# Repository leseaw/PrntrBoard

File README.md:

Prntr Board V1
======================
PrntrBoard is a 3D printer controller board designed to work as a shield to STM32 NUCLEO-64 F446 dev kit.

Some features of the board:
-----
  + 5x Trinamic super quiet drivers (TMC2130 or TMC2660)
  + Marlin firmware
  + (2+2) controllable fans and 2x "always on" fan connectors
  + 3x min and max endstops for the x, y and z axis
  + 2x end stops for fillament end detection
  + SPI lcd connector for ST7735 screen
  + Dual thermocouple connectors (for MAX31866, MAX31855 or MAX6675 boards)
  + selectable fan voltage (5V or Vin)

Because the NUCLEO-64 has limited number of IO pins, some compromises had to be made:
  + No sd-card
  + The thermocouple connectors share pins with the E0 and E1 cool fan controls. You'll have to decide to use one or the other via jumpers on the board. Most printers I've seen come with "always on" extruder fans, the choice seemed like a worthy sacrifice.

Generic shortcuts I don't plan to improve:
------
  + 5V power supply is external. These are available from various resellers and fairly cheap - less than $1. No need to waste board layout space and component count.
  + Heated bed MOSFET - large heated beds consume a lot of power and it is challenging to provision the design for > 10A current. External heated bed MOSFETs are very affordable < $10 and claim to support 20A minimum. If you have large bet use one.

Details
------
I use the daily build of KiCad (soon to be released V5) - let me know if you have trouble opening the files.

The current PCB desing is using 4 layer board, 6/6 mil track width/clearance, 12 mil min via hole size and 20 mil via diameter.

There are two active branches:
  + tmc2130 - the board design for TMC2130 drivers
  + tmc2660 - the board design for TMC2660 drivers
  + branches with -r\<digit> sufix are snapshots of boards I have ordered. I only do "minimal" changes there to generate better manufacturing files (for example renaming a component).

Both PCB designs use the QFP version of the driver ICs, because they can handle a bit more power.

Status
------
Rev2 is the current working version. Rev1 had a bug in the endstop input design, other that that it is able to control a 3D printer successfully. I'm considering a re-design of the layout - swapping the location of the 5V input connector and the E1 driver. The driver is crammed in the corner and there was not a lot of space for heat disipation, by moving it to the right there is more breading room. Also considering rotating the NUCLEO board, so it does not stick up in this unpleasant manner.

Tested circuits:
  + Heater control
  + Thermistor input
  + Fan control
  + Motor driver control
  + End stops

Circuits that need verification:
  + Stall guard alert from the motor driver
  + Z probe
  + LCD interface (I noticed this may interfere with the 32k chrystal on the nucleo board)
  + Thermocuple interface

Software
------

The software for the board is a clone of Marlin at [bugfix-2.0.x branch](https://github.com/ghent360/Marlin/tree/bugfix-2.0.x/ "Github.com") of my repository. I keep it relatively in sync with the Marlin branch. *Note: there are other branches of Marlin as well only the bugfix-2.0.x supports the STM32 microcontroller.*

Marlin is using Adruino IDE or Platform IO. I personally had issues with Platform IO not supporting the STM32F4 board, so I use Arduino version 1.8.5. To compile the firmware code you would need to install the [STM32 Arduino port](https://github.com/stm32duino/Arduino_Core_STM32 "www.stm32duino.com").

Visit [my blog](http://blog.pcbxprt.com/) for status updates on the development of the board. I have video of the board controlling a Duplicator I3 mini.

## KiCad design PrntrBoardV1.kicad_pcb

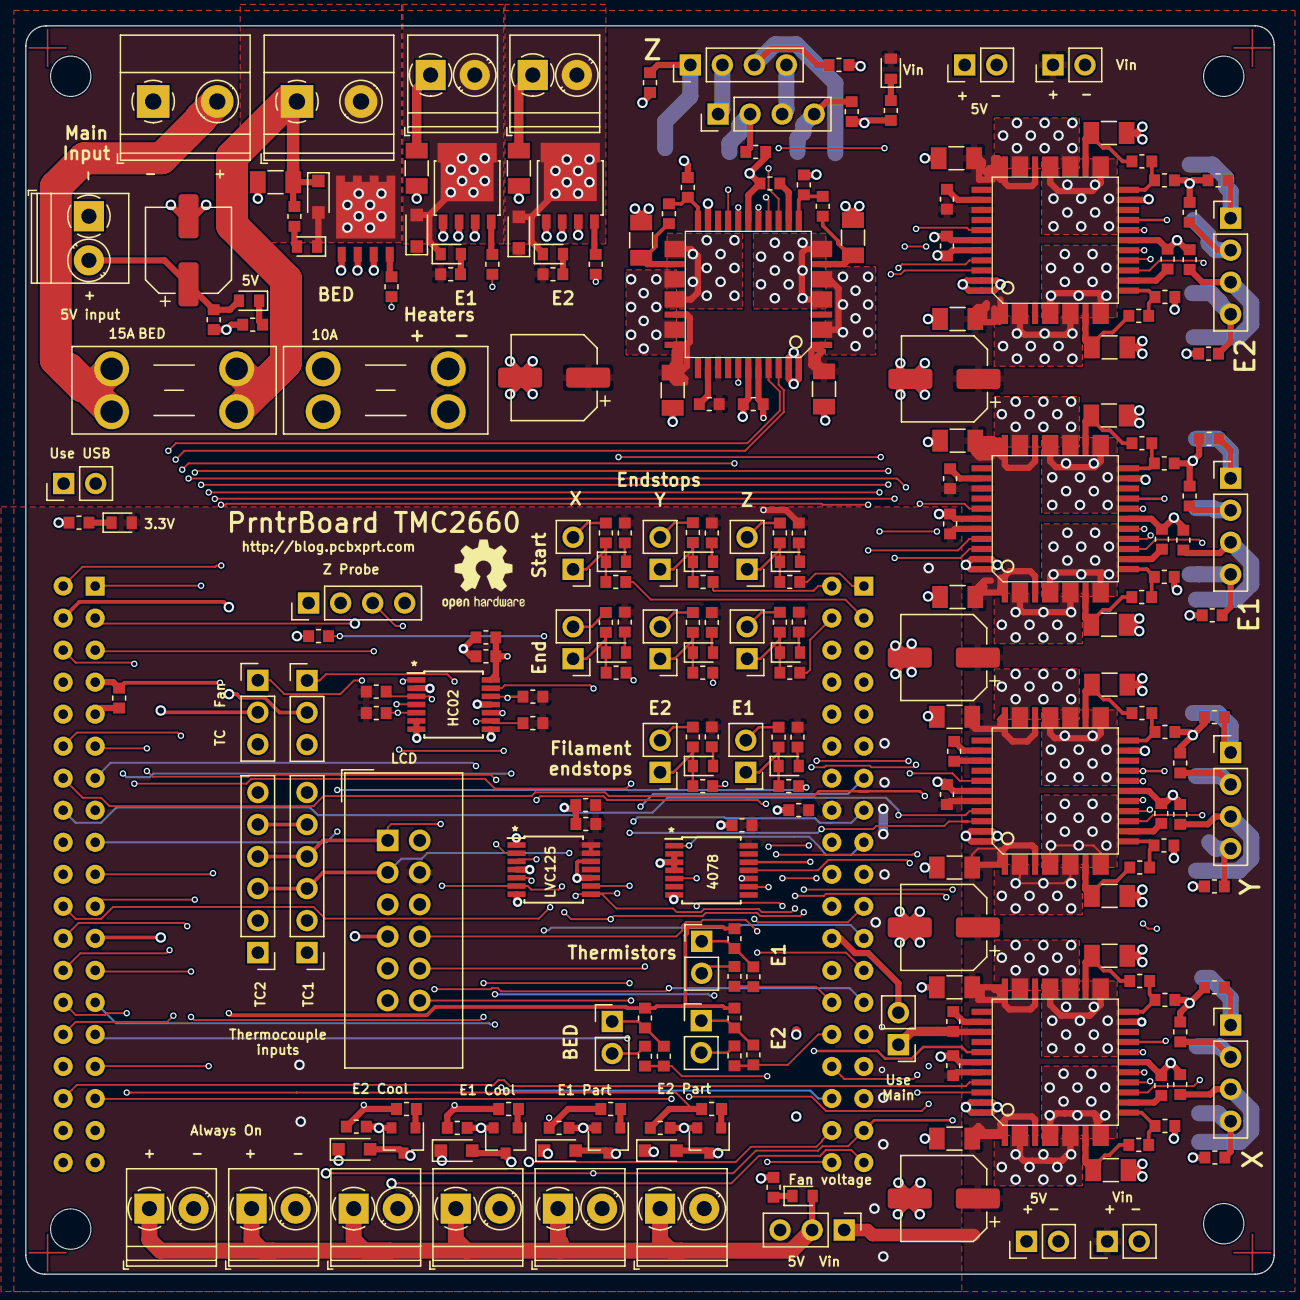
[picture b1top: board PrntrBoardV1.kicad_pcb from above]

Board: 4 copper layers, 99.0 x 99.0 mm, 238 parts (1 on the bottom side), 165 nets.

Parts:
C1, C5: 10uF 10V; C_0603_1608Metric
C2: 100uF; CP_Elec_6.3x7.7
C3, C6, C8, C22, C23, C37, C38, C51, C52, C65, C66, C79, C80, C82: 1000pF; C_0603_1608Metric
C4, C7, C9, C15, C30, C44, C58, C72: 0.1uF; C_0603_1608Metric
C10, C11, C24, C25, C26, C39, C40, C53, C54, C67, C68, C81, C83: 10uF 50V; C_1206_3216Metric
C12, C27, C41, C55, C69: 100uF 35V; CP_Elec_6.3x7.7
C13, C28, C42, C56, C70: 0.1uF 50V; C_0603_1608Metric
C14, C29, C43, C57, C71: 0.47uF; C_0603_1608Metric
C16, C21, C31, C36, C45, C50, C59, C64, C73, C78: 0.01uF X7R 10% 50V; C_0603_1608Metric
C17, C18, C19, C20, C32, C33, C34, C35, C46, C47, C48, C49, C60, C61, C62, C63, C74, C75, C76, C77: 1000pF >50V; C_0603_1608Metric
D1, D2, D3, D4, D5, D6, D8, D9, D10, D11, D12, D13, D14, D15, D17: LED; LED_0603_1608Metric
D7, D16, D18, D19, D20, D21, D22: 1N4148; D_SOD-323_HandSoldering
F1: 10A; Fuseholder_Blade_Mini_Keystone_3568
F2: 15A; Fuseholder_Blade_Mini_Keystone_3568
FID1, FID2, FID3, FID4: Fiducial; Fiducial_1mm_Dia_2.54mm_Outer_CopperTop
J1: 12-24V; TerminalBlock_Phoenix_MKDS-1,5-2-5.08_1x02_P5.08mm_Horizont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
J2: EXT 5V; TerminalBlock_Phoenix_PT-1,5-2-3.5-H_1x02_P3.50mm_Horizontal
J3, J4: Vin; PinHeader_1x02_P2.54mm_Vertical
J5, J6: 5V; PinHeader_1x02_P2.54mm_Vertical
J7: Bed Heater; TerminalBlock_Phoenix_MKDS-1,5-2-5.08_1x02_P5.08mm_Horizont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
J8: Z Probe; PinHeader_1x04_P2.54mm_Vertical
J9: E0 Cool; TerminalBlock_Phoenix_PT-1,5-2-3.5-H_1x02_P3.50mm_Horizontal
J10: E0 Part; TerminalBlock_Phoenix_PT-1,5-2-3.5-H_1x02_P3.50mm_Horizontal
J11: E1 Cool; TerminalBlock_Phoenix_PT-1,5-2-3.5-H_1x02_P3.50mm_Horizontal
J12: E1 Part; TerminalBlock_Phoenix_PT-1,5-2-3.5-H_1x02_P3.50mm_Horizontal
J13: Always On Fan 1; TerminalBlock_Phoenix_PT-1,5-2-3.5-H_1x02_P3.50mm_Horizontal
J14: Always On Fan 2; TerminalBlock_Phoenix_PT-1,5-2-3.5-H_1x02_P3.50mm_Horizontal
J15: TC1; PinHeader_1x06_P2.54mm_Vertical
J16: TC2; PinHeader_1x06_P2.54mm_Vertical
J17, J31: Probe; PinHeader_1x02_P2.54mm_Vertical
J18, J32: Extruder Heater; TerminalBlock_Phoenix_PT-1,5-2-3.5-H_1x02_P3.50mm_Horizontal
J19, J27, J28, J29, J30, J33: Stepper; PinHeader_1x04_P2.54mm_Vertical
J20, J34, J35: Thermistor; PinHeader_1x02_P2.54mm_Vertical
J21, J23, J25: Max; PinHeader_1x02_P2.54mm_Vertical
J22, J24, J26: Min; PinHeader_1x02_P2.54mm_Vertical
J36: LCD; IDC-Header_2x06_P2.54mm_Vertical
JP1: E1_TC2; PinHeader_1x03_P2.54mm_Vertical
JP2: Use VIn; PinHeader_1x02_P2.54mm_Vertical
JP3: Use USB; PinHeader_1x02_P2.54mm_Vertical
JP4: E0_TC1; PinHeader_1x03_P2.54mm_Vertical
JP5: FAN Voltage select; PinHeader_1x03_P2.54mm_Vertical
LOGO1: Logo_Open_Hardware_Large; OSHW-Logo2_7.3x6mm_SilkScreen
MK1: Mounting_Hole; MountingHole_3.2mm_M3
MK2, MK3, MK4: Mounting_Hole_3mm; MountingHole_3.2mm_M3
R1, R3, R4, R5, R6, R7, R9, R15, R17, R19, R25, R27, R33, R35, R41, R43, R49, R51, R53, R55, R57, R58, R60, R62, R64: 10k; R_0603_1608Metric
R2, R8, R14, R24, R26, R32, R34, R40, R42, R48, R59, R61, R63, R65: 1k; R_0603_1608Metric
R10, R12, R20, R22, R28, R30, R36, R38, R44, R46: 22R; R_0603_1608Metric
R11, R13, R21, R23, R29, R31, R37, R39, R45, R47: 0R051; R_1206_3216Metric
R16, R50, R54: 4k7 1%; R_0603_1608Metric
R18, R52, R56: 180R; R_0603_1608Metric
TR1, TR2: PSMN7R0-30YL; SOT-669_LFPAK
TR3: BSC011N03LS; PG-TDSON-8-FL
TR4, TR5, TR6, TR7: SI2318CDS; SOT-23
U1: NUCLEO-64; Nucleo-64
U2: 4078; TSSOP-14_4.4x5mm_P0.65mm
U3: 74HCT02; TSSOP-14_4.4x5mm_P0.65mm
U4: 74LVC125; TSSOP-14_4.4x5mm_P0.65mm
U5, U6, U7, U8, U9: TMC2660

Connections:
/3.3V: C1.1, C4.1, C8.1, C9.1, C15.1, C30.1, C44.1, C58.1, C72.1, D2.2, J36.4, R3.1, R4.1, R5.1, R6.1, R14.1, R24.1, R26.1, R32.1, R34.1, R40.1, R42.1, R48.1, U1.16, U2.14, U4.13, U4.14, U5.40, U6.40, U7.40, U8.40, U9.40
/5V: C2.1, C3.1, C6.1, C7.1, D3.2, J2.2, J5.1, J6.1, J8.4, J15.1, J16.1, J36.2, JP3.2, JP5.3, U1.6, U3.14
/AVREF: C5.1, R16.1, R50.1, R54.1, U1.45
/BED_PWM_IN: R6.2, U1.34, U3.5
/BED_TEMP: C82.1, R55.1, U1.38
/BTN_IN: J36.8, U1.25
/E0 Cooling Fan/OUT: D19.2, J9.2, TR4.D
/E0 Cooling Fan/V_FAN: D4.2, D19.1, D20.1, D21.1, D22.1, J9.1, J10.1, J11.1, J12.1, J13.1, J14.1, JP5.2
/E0 Part Fan/OUT: D20.2, J10.2, TR5.D
/E0_COOL_PWM: JP4.1, R58.1, R59.2
/E0_COOL_TC1: JP4.2, U1.42
/E0_DIR: U1.40, U5.41
/E0_END: R15.1, U1.55
/E0_PART_PWM: R60.1, R61.2, U1.60
/E0_PWM: R18.2, U3.10
/E0_PWM_IN: R4.2, U1.51, U3.9
/E0_STEP: U1.57, U5.42
/E0_TEMP: C23.1, R17.1, U1.28
/E1 Cooling Fan/OUT: D21.2, J11.2, TR6.D
/E1 Part Fan/OUT: D22.2, J12.2, TR7.D
/E1_COOL_PWM: JP1.1, R62.1, R63.2
/E1_COOL_TC2: JP1.2, U1.61
/E1_DIR: U1.59, U9.41
/E1_END: R49.1, U1.21
/E1_PART_PWM: R64.1, R65.2, U1.66
/E1_PWM: R52.2, U3.13
/E1_PWM_IN: R5.2, U1.53, U3.12
/E1_STEP: U1.39, U9.42
/E1_TEMP: C80.1, R51.1, U1.30
/ENC_A: J36.10, U1.13
/ENC_B: J36.12, U1.15
/Heated Bed/HEATER: D17.1, D18.2, J7.2, TR3.D
/Heated Bed/PWM: R56.2, U3.4
/Heated Bed/V_HEAT: C83.1, D18.1, F2.2, J7.1, R57.1
/LCD_A0: J36.5, U1.43
/MISO: J15.5, J16.5, U1.35, U5.14, U6.14, U7.14, U8.14, U9.14
/MOSI: U1.36, U4.5
/MOSI_BUF: J15.4, J16.4, J36.1, U4.6, U5.15, U6.15, U7.15, U8.15, U9.15
/MotorControl/E0/Driver/MOTA1: C17.2, J19.3, U5.2.3, U5.7.8
/MotorControl/E0/Driver/MOTA2: C18.2, J19.4, U5.5.6, U5.10.1
/MotorControl/E0/Driver/MOTB1: C19.2, J19.1, U5.26.7, U5.31.2
/MotorControl/E0/Driver/MOTB2: C20.2, J19.2, U5.23.4, U5.28.9
/MotorControl/E0/Fimalent Detect/SENSOR: C22.1, D5.1, J17.1, R15.2
/MotorControl/E0/Heating/HEATER: D6.1, D7.2, J18.2, TR1.D
/MotorControl/E0/~ENABLE: U4.3, U5.19, U6.19, U7.19, U8.19, U9.19
/MotorControl/E0_SG: U2.9, U5.38
/MotorControl/E1/Driver/MOTA1: C74.2, J33.3, U9.2.3, U9.7.8
/MotorControl/E1/Driver/MOTA2: C75.2, J33.4, U9.5.6, U9.10.1
/MotorControl/E1/Driver/MOTB1: C76.2, J33.1, U9.26.7, U9.31.2
/MotorControl/E1/Driver/MOTB2: C77.2, J33.2, U9.23.4, U9.28.9
/MotorControl/E1/Fimalent Detect/SENSOR: C79.1, D14.1, J31.1, R49.2
/MotorControl/E1/Heating/HEATER: D15.1, D16.2, J32.2, TR2.D
/MotorControl/E1_SG: U2.5, U9.38
/MotorControl/X Axis/MOTA1: C32.2, J27.3, U6.2.3, U6.7.8
/MotorControl/X Axis/MOTA2: C33.2, J27.4, U6.5.6, U6.10.1
/MotorControl/X Axis/MOTB1: C34.2, J27.1, U6.26.7, U6.31.2
/MotorControl/X Axis/MOTB2: C35.2, J27.2, U6.23.4, U6.28.9
/MotorControl/X Axis/MaxStop/SENSOR: C37.1, D8.1, J21.1, R25.2
/MotorControl/X Axis/MinStop/SENSOR: C38.1, D9.1, J22.1, R27.2
/MotorControl/X_SG: U2.12, U6.38
/MotorControl/Y Axis/MOTA1: C46.2, J28.3, U7.2.3, U7.7.8
/MotorControl/Y Axis/MOTA2: C47.2, J28.4, U7.5.6, U7.10.1
/MotorControl/Y Axis/MOTB1: C48.2, J28.1, U7.26.7, U7.31.2
/MotorControl/Y Axis/MOTB2: C49.2, J28.2, U7.23.4, U7.28.9
/MotorControl/Y Axis/MaxStop/SENSOR: C51.1, D10.1, J23.1, R33.2
/MotorControl/Y Axis/MinStop/SENSOR: C52.1, D11.1, J24.1, R35.2
/MotorControl/Y_SG: U2.11, U7.38
/MotorControl/Z Axis/MOTA1: C60.2, J30.3, U8.2.3, U8.7.8
/MotorControl/Z Axis/MOTA2: C61.2, J29.4, U8.5.6, U8.10.1
/MotorControl/Z Axis/MOTB1: C62.2, J30.1, U8.26.7, U8.31.2
/MotorControl/Z Axis/MOTB2: C63.2, J29.2, U8.23.4, U8.28.9
/MotorControl/Z Axis/MaxStop/SENSOR: C65.1, D12.1, J25.1, R41.2
/MotorControl/Z Axis/MinStop/SENSOR: C66.1, D13.1, J26.1, R43.2
/MotorControl/Z Motors/Motor1/MOTA1: J29.3, J30.4
/MotorControl/Z Motors/Motor1/MOTB1: J29.1, J30.2
/MotorControl/Z_SG: U2.10, U8.38
/SCK: U1.63, U4.9
/SCK_BUF: J15.3, J16.3, J36.3, U4.8, U5.16, U6.16, U7.16, U8.16, U9.16
/STALL: U1.17, U2.1
/VBUS: JP3.1, U1.46
/V_MOTORS: C10.1, C11.1, C12.1, C13.1, C24.1, C25.1, C26.1, C27.1, C28.1, C39.1, C40.1, C41.1, C42.1, C53.1, C54.1, C55.1, C56.1, C67.1, C68.1, C69.1, C70.1, C81.1, D1.2, D7.1, D16.1, F1.1, J3.1, J4.1, J18.1, J32.1, JP2.1, JP5.1, R19.1, R53.1, U5.1, U5.4, U5.30, U5.33, U5.36, U6.1, U6.4, U6.30, U6.33, U6.36, U7.1, U7.4, U7.30, U7.33, U7.36, U8.1, U8.4, U8.30, U8.33, U8.36, U9.1, U9.4, U9.30, U9.33, U9.36
/Vin: F1.2, F2.1, J1.2
/X_DIR: U1.72, U6.41
/X_END: R25.1, U1.4
/X_START: R27.1, U1.1
/X_STEP: U1.32, U6.42
/Y_DIR: U1.54, U7.41
/Y_END: R33.1, U1.65
/Y_START: R35.1, U1.2
/Y_STEP: U1.44, U7.42
/Z_DIR: U1.64, U8.41
/Z_END: R41.1, U1.67
/Z_PROBE_IN: R8.1, U1.23
/Z_PROBE_MOD: R3.2, U1.27, U3.3
/Z_PROBE_MOD_BUF: J8.3, U3.1
/Z_START: R43.1, U1.3
/Z_STEP: U1.68, U8.42
/~E0_CS: U1.69, U5.18
/~E1_CS: U1.62, U9.18
/~EN_MOTORS: U1.49, U4.2
/~LCD_CS: J36.9, U1.37
/~LCD_RESET: J36.7, U1.41
/~TC1_CS: J15.6, JP4.3
/~TC2_CS: J16.6, JP1.3
/~X_CS: U1.71, U6.18
/~Y_CS: U1.52, U7.18
/~Z_CS: U1.50, U8.18
GND: C1.2, C2.2, C3.2, C4.2, C5.2, C6.2, C7.2, C8.2, C9.2, C10.2, C11.2, C12.2, C14.1, C15.2, C16.2, C17.1, C18.1, C19.1, C20.1, C21.2, C22.2, C23.2, C24.2, C25.2, C26.2, C27.2, C29.1, C30.2, C31.2, C32.1, C33.1, C34.1, C35.1, C36.2, C37.2, C38.2, C39.2, C40.2, C41.2, C43.1, C44.2, C45.2, C46.1, C47.1, C48.1, C49.1, C50.2, C51.2, C52.2, C53.2, C54.2, C55.2, C57.1, C58.2, C59.2, C60.1, C61.1, C62.1, C63.1, C64.2, C65.2, C66.2, C67.2, C68.2, C69.2, C71.1, C72.2, C73.2, C74.1, C75.1, C76.1, C77.1, C78.2, C79.2, C80.2, C81.2, C82.2, C83.2, J1.1, J2.1, J3.2, J4.2, J5.2, J6.2, J8.2, J13.2, J14.2, J15.2, J16.2, J17.2, J20.2, J21.2, J22.2, J23.2, J24.2, J25.2, J26.2, J31.2, J34.2, J35.2, J36.6, J36.11, R1.2, R2.1, R7.2, R9.2, R11.2, R13.2, R21.2, R23.2, R29.2, R31.2, R37.2, R39.2, R45.2, R47.2, R58.2, R60.2, R62.2, R64.2, TR1.S, TR2.S, TR3.S, TR4.S, TR5.S, TR6.S, TR7.S, U1.8, U1.19, U1.20, U1.22, U1.47, U1.58, U1.70, U2.2, U2.3, U2.4, U2.7, U3.2, U3.6, U3.7, U3.8, U3.11, U4.1, U4.4, U4.7, U4.10, U4.12, U5.17, U5.21, U5.39, U5.43, U5.44, U6.17, U6.21, U6.39, U6.43, U6.44, U7.17, U7.21, U7.39, U7.43, U7.44, U8.17, U8.21, U8.39, U8.43, U8.44, U9.17, U9.21, U9.39, U9.43, U9.44
unnamed: C13.2, U5.35
unnamed: C14.2, U5.13
unnamed: C16.1, R10.1, U5.22
unnamed: C21.1, R12.1, U5.12
unnamed: C28.2, U6.35
unnamed: C29.2, U6.13
unnamed: C31.1, R20.1, U6.22
unnamed: C36.1, R22.1, U6.12
unnamed: C42.2, U7.35
unnamed: C43.2, U7.13
unnamed: C45.1, R28.1, U7.22
unnamed: C50.1, R30.1, U7.12
unnamed: C56.2, U8.35
unnamed: C57.2, U8.13
unnamed: C59.1, R36.1, U8.22
unnamed: C64.1, R38.1, U8.12
unnamed: C70.2, U9.35
unnamed: C71.2, U9.13
unnamed: C73.1, R44.1, U9.22
unnamed: C78.1, R46.1, U9.12
unnamed: D1.1, R1.1
unnamed: D2.1, R2.2
unnamed: D3.1, R7.1
unnamed: D4.1, R9.1
unnamed: D5.2, R14.2
unnamed: D6.2, R19.2
unnamed: D8.2, R24.2
unnamed: D9.2, R26.2
unnamed: D10.2, R32.2
unnamed: D11.2, R34.2
unnamed: D12.2, R40.2
unnamed: D13.2, R42.2
unnamed: D14.2, R48.2
unnamed: D15.2, R53.2
unnamed: D17.2, R57.2
unnamed: J8.1, R8.2
unnamed: J20.1, R16.2, R17.2
unnamed: J34.1, R50.2, R51.2
unnamed: J35.1, R54.2, R55.2
unnamed: JP2.2, U1.24
unnamed: R10.2, R11.1, U5.25
unnamed: R12.2, R13.1, U5.9
unnamed: R18.1, TR1.G
unnamed: R20.2, R21.1, U6.25
unnamed: R22.2, R23.1, U6.9
unnamed: R28.2, R29.1, U7.25
unnamed: R30.2, R31.1, U7.9
unnamed: R36.2, R37.1, U8.25
unnamed: R38.2, R39.1, U8.9
unnamed: R44.2, R45.1, U9.25
unnamed: R46.2, R47.1, U9.9
unnamed: R52.1, TR2.G
unnamed: R56.1, TR3.G
unnamed: R59.1, TR4.G
unnamed: R61.1, TR5.G
unnamed: R63.1, TR6.G
unnamed: R65.1, TR7.G

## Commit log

2018-04-15 Added clock line for the motor drivers.
2018-04-15 Annotate schematics. Select footprints for the added jumpers.
2018-04-15 All routed again. Clock jumpers on the bottom side.
2018-04-15 Add motorl clock jumper labels.
2018-05-04 Added gerber files and Pick and Place file.
2018-05-04 Set board origin.
2018-05-09 Update connector components. Correct bad capacitor value.
2018-06-21 Updated README.md.
2018-06-23 Add pick-and-place output file.
2018-06-23 Update FID* to SMD from virtual component, so they show up in the pick-and-place output.
2018-06-23 Add 3D models locally compresed.
2018-06-23 Fixed some project paths to pint to the current project folder.
2018-06-23 Add some exotic 74xxx components.
2018-06-23 Complete path cleanup.
2018-06-23 Rename some somponents to suite PNP process.
2018-06-23 Update FID* to SMD from virtual, so it shows on the PnP file. Set axis origin.
2018-06-24 Cherry pick path names changes.
2018-06-24 Ignore uncompressed 3D model files.
2018-07-02 Fix endstops.
2018-07-02 Update board with the new endstop configuration.
2018-07-03 Updated readme file.
2018-07-03 Cleared sentence on the top.
2019-01-21 Added two fuses, because we have space.
2019-01-21 Add the Fuse holder model.
